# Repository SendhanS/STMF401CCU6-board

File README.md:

# STMF401CCU6-board
STM32F4 series breakout board

The breakout board is based on the STM32F401CCU6 microcontroller in a QFN-48 package, chosen
for its high-performance ARM Cortex-M4 core and compact footprint, providing sufficient digital and
communication interfaces for typical embedded applications while fitting within the 50 × 50 mm
board area. Power regulation is handled by the TLV75801PDRV low-dropout linear regulator, selected
for its compact SOT-23-5 package and ability to convert a 5 V input from USB or header to a stable
3.3 V supply required by the STM32F401 and peripherals.
Peripheral pin mapping follows assignment specifications: five GPIO outputs, I2C1 on PB6/PB7, SPI1
on PA5/PA6/PA7, USART2 on PA2/PA3, and SWD interface on a 2×5 header including SWDIO, SWCLK,
SWO, NRST, 3.3 V, and GND. To minimize routing complexity, peripherals are mapped to ensure all
related pins are on the same side of the MCU, preventing excessive trace crossings and overlap. The
reset button is connected to NRST with a parallel 0.1 μF capacitor, and a user LED is connected to
PC13 via a 1.5 kΩ series resistor.
Power and layout considerations prioritize clean routing and manufacturability. The 3.3 V rail is
decoupled with four 100 nF capacitors near the MCU and a 10 μF bulk capacitor at the
TLV75801PDRV output. The 8 MHz crystal is placed close to the MCU with a restricted area around its
traces to prevent noise coupling. A solid GND pour covers both layers, connecting decoupling caps,
mounting holes, and headers. Trace widths are 0.4 mm for power and 0.15–0.2 mm for signals,
following standard PCB design practice.

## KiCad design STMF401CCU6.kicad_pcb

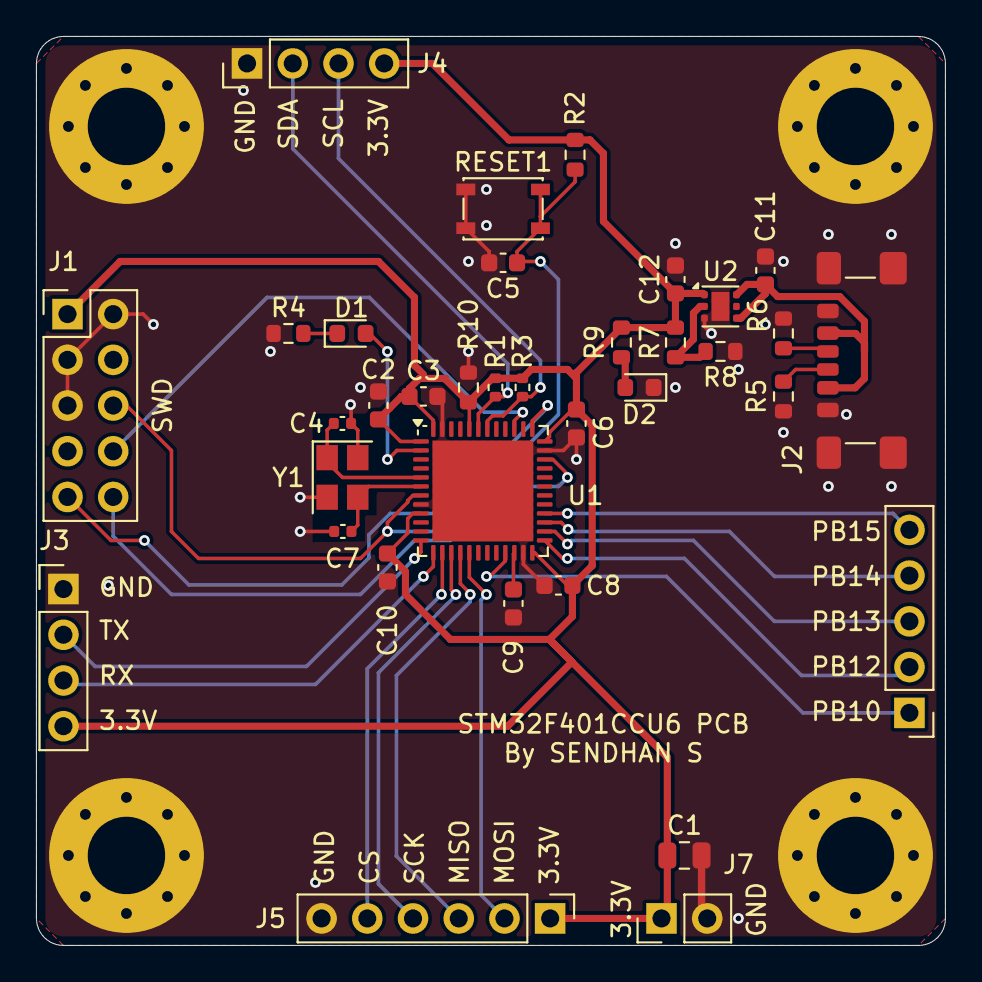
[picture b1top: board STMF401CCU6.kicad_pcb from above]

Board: 2 copper layers, 50.5 x 50.5 mm, 39 parts (0 on the bottom side), 29 nets.

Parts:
3.3V: SPI; PinHeader_1x06_P2.54mm_Vertical
C1: 10uf; C_0805_2012Metric
C2, C3, C6, C8, C10: 100nf; C_0603_1608Metric
C4, C7: 12p; C_0402_1005Metric
C5: 0.1uf; C_0603_1608Metric
C9: 4.7uf; C_0603_1608Metric
C11, C12: 10uF; C_0603_1608Metric
D1: BLUE; LED_0603_1608Metric
D2: LED; LED_0603_1608Metric
GND: Conn_01x02_Pin; PinHeader_1x02_P2.54mm_Vertical
GND#2: I2C; PinHeader_1x04_P2.54mm_Vertical
H1, H2, H3, H4: MountingHole_Pad; MountingHole_4.3mm_M4_Pad_Via
J2: USB_C_Receptacle_PowerOnly_6P; USB_C_Receptacle_GCT_USB4135-GF-A_6P_TopMnt_Horizontal
J3: USART2; PinHeader_1x04_P2.54mm_Vertical
PB10: Digital Output; PinHeader_1x05_P2.54mm_Vertical
R1, R3: 4.7k; R_0402_1005Metric
R2, R10: 10k; R_0603_1608Metric
R4: 1.5k; R_0603_1608Metric
R5, R6, R9: 5.1k; R_0603_1608Metric
R7: 1M; R_0603_1608Metric
R8: 200k; R_0603_1608Metric
RESET1: SW_SPST_PTS810
SWD: SWD; PinHeader_2x05_P2.54mm_Vertical
U1: STM32F401CCUx; QFN-48-1EP_7x7mm_P0.5mm_EP5.6x5.6mm
U2: TLV75801PDRV; WSON-6-1EP_2x2mm_P0.65mm_EP1x1.6mm
Y1: 8MHz; Crystal_SMD_3225-4Pin_3.2x2.5mm

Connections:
/3V3: 3.3V.1, C1.1, C2.1, C3.1, C6.1, C8.1, C10.1, C12.1, GND.1, GND#2.4, J3.4, R1.1, R2.2, R3.1, R7.2, R9.1, R10.1, SWD.1, U1.1 (VBAT), U1.9 (VREF+), U1.24 (VDD), U1.36 (VDD), U1.44 (BOOT0), U1.48 (VDD), U2.1 (OUT)
/5VUSB: C11.1, J2.A9 (VBUS), J2.B9 (VBUS), U2.4 (EN), U2.6 (IN)
/CS: 3.3V.5, U1.14 (PA4)
/MISO: 3.3V.3, U1.16 (PA6)
/MOSI: 3.3V.2, U1.17 (PA7)
/NRST: C5.2, R2.1, RESET1.3 (K), RESET1.4 (A), SWD.6, U1.7 (NRST)
/PB10: PB10.1, U1.21 (PB10)
/PB12: PB10.2, U1.25 (PB12)
/PB13: PB10.3, U1.26 (PB13)
/PB14: PB10.4, U1.27 (PB14)
/PB15: PB10.5, U1.28 (PB15)
/RX: J3.3, U1.13 (PA3)
/SCK: 3.3V.4, U1.15 (PA5)
/SCL: GND#2.3, R3.2, U1.42 (PB6)
/SDA: GND#2.2, R1.2, U1.43 (PB7)
/SWCLK: SWD.9, U1.37 (PA14)
/SWDIO: SWD.10, U1.34 (PA13)
/SWO: SWD.8, U1.39 (PB3)
/TX: J3.2, U1.12 (PA2)
/USER_LED: D1.2 (A), U1.2 (PC13)
GND: 3.3V.6, C1.2, C2.2, C3.2, C4.2, C5.1, C6.2, C7.2, C8.2, C9.2, C10.2, C11.2, C12.2, D2.1 (K), GND.2, GND#2.1, H1.1, H2.1, H3.1, H4.1, J2.A12 (GND), J2.B12 (GND), J2.S1 (SHIELD), J3.1, R4.1, R5.2, R6.2, R8.1, R10.2, RESET1.1, RESET1.2, SWD.2, SWD.3, SWD.5, U1.8 (VSSA), U1.23 (VSS), U1.35 (VSS), U1.47 (VSS), U1.49 (VSS), U2.3 (GND), U2.7 (GND), Y1.2, Y1.4
unnamed: D1.1 (K), R4.2
unnamed: D2.2 (A), R9.2
unnamed: J2.A5 (CC1), R5.1
unnamed: J2.B5 (CC2), R6.1
unnamed: C4.1, U1.5 (PH0), Y1.1
unnamed: C7.1, U1.6 (PH1), Y1.3
unnamed: C9.1, U1.22 (VCAP1)
unnamed: R7.1, R8.2, U2.2 (FB)

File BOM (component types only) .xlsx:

Designator | Package | Value
J4 | 1×6 pin header | SPI
C1 | 0805 SMD | 10uf
C10, C2, C3, C6, C8 | 0603 SMD | 100nf
C11, C12 | 0603 SMD | 10uF
C4, C7 | 0402 SMD | 12p
C5 | 0603 SMD | 0.1uf
C9 | 0603 SMD | 4.7uf
D1 | 0603 SMD LED | BLUE
D2 | 0603 SMD LED | LED
J7 | 1×2 pin header | Conn_01x02_Pin
J4 | 1×4 pin header | I2C
H1, H2, H3, H4 | 4.3 mm mounting hole for M4 | MountingHole_Pad
J2 | USB-C 6P SMT | USB_C_Receptacle_PowerOnly_6P
J3 | 1×4 pin header | USART2
J6 | 1×5 pin header | Digital Output
R1, R3 | 0402 SMD resistor | 4.7k
R10, R2 | 0603 SMD resistor | 10k
R4 | 0603 SMD resistor | 1.5k
R5, R6, R9 | 0603 SMD resistor | 5.1k
R7 | 0603 SMD resistor | 1M
R8 | 0603 SMD resistor | 200k
RESET1 | SPST switch -SMT | ~
J1 | 2×5 pin header | SWD
U1 | QFN-48, 7×7 mm | STM32F401CCUx
U2 | WSON-6, 2×2 mm | TLV75801PDRV
Y1 | SMD 3225 4-pin crystal, 3.2×2.5 mm | 8MHz
